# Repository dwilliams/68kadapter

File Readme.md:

# 68030 to 68020 adapter

Barebones adapter for Motorola processors, converting 68030 to 68020. There is no logic in this, and all the extra features of the 68030 are disabled.

# Why was this made?

To be used with [https://rosco-m68k.com/](https://rosco-m68k.com/) 68020 SBC to test CPUs bought off eBay. Didn't want to buy both the '20 and the '30 version, and now I can test (to a large degree) both versions. The MMU isn't getting tested, but in practice the chips either all work or fail completely to even come up, so it met it's goal.

# Headers and socket

You can buy those off sites like DigiKey or eBay.

For the plug-in 68020 side I used 2.54 mm Single Row Male Pin Headers that I cut up to fill in the rows/columns as needed. They need to be aligned really well otherwise it's close to impossible to plug them into a socket. I used one of the non-populated boards (got 3 made for corrections, test, etc) to hold the pins in place in the right way, but you can also use a 68020 socket and get the same effect. The latter might be too much of a heat sink though, making soldering hard.

The 68030 side is just a regular 128 Pin Machine Pin Grid Array PGA IC Socket.

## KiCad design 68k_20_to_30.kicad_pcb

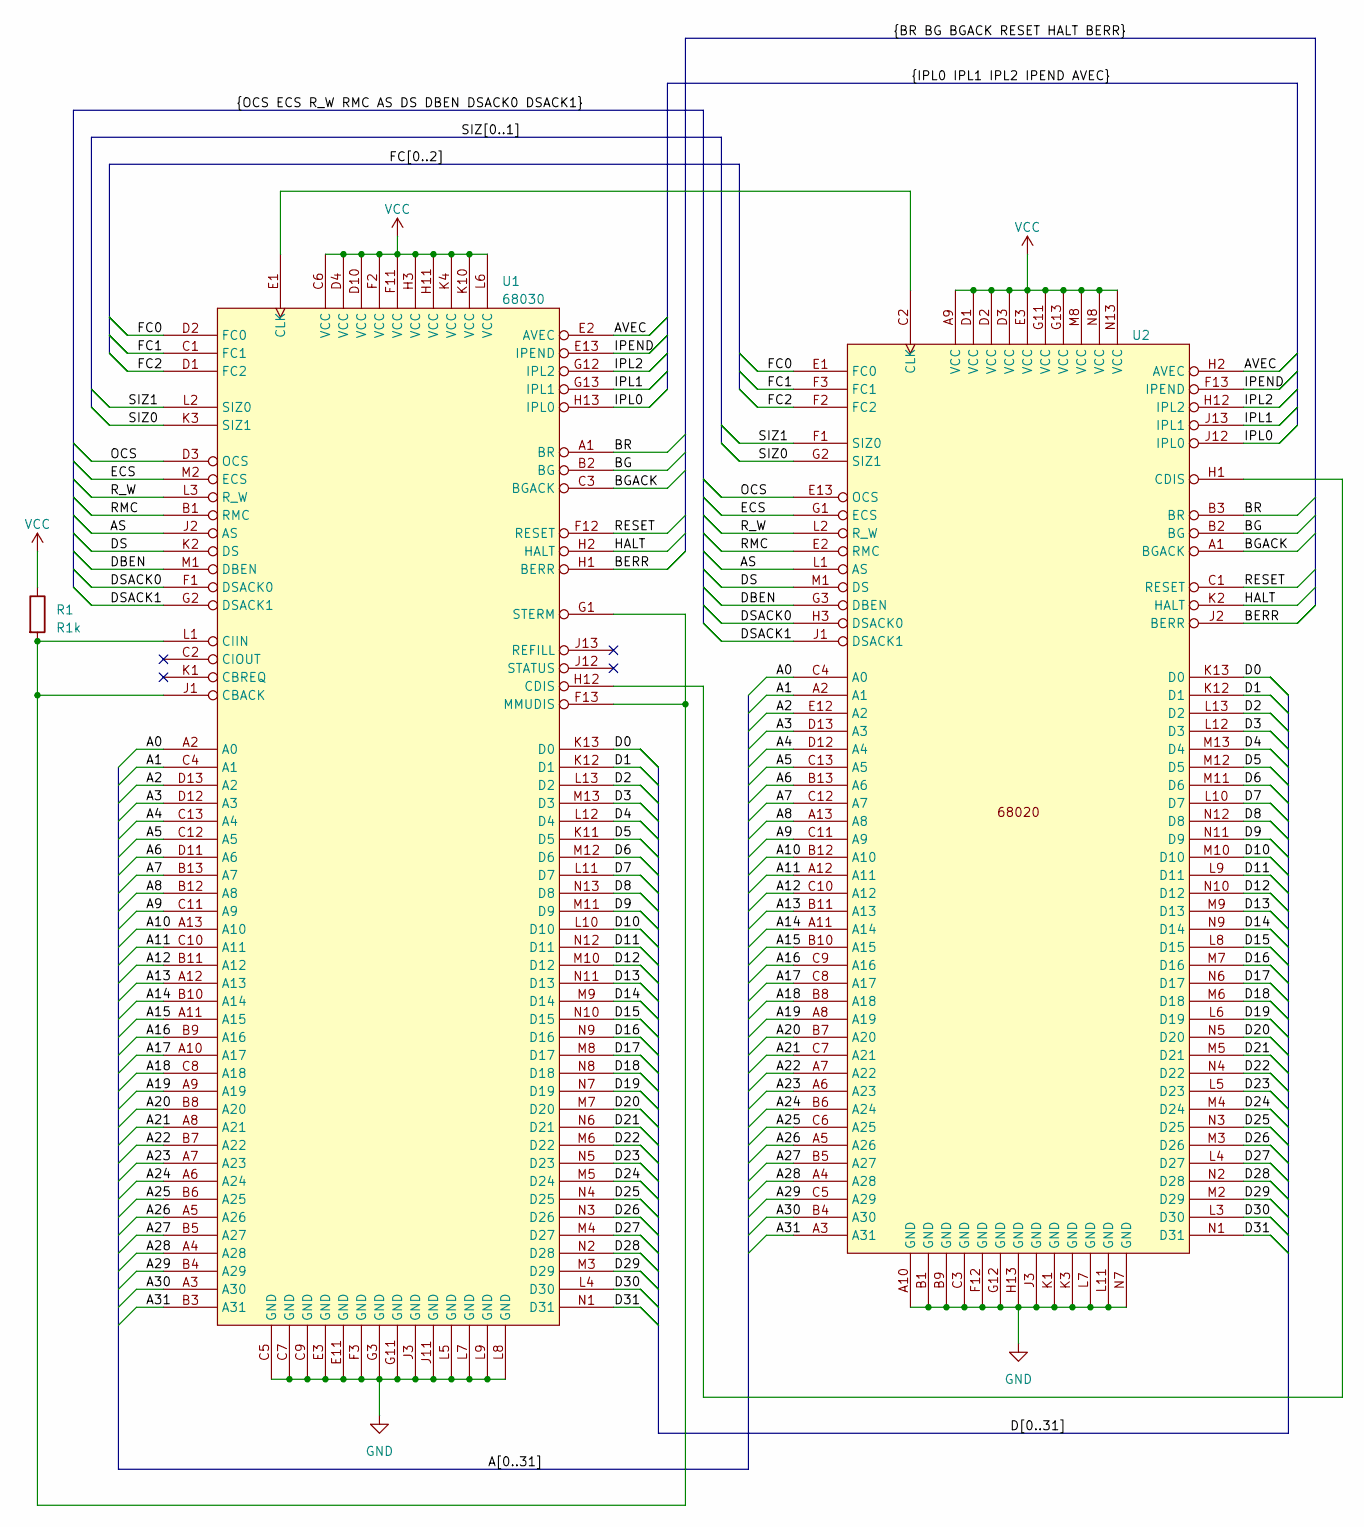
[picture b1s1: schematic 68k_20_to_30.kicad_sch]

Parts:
R1: R1k; R_Axial_DIN0204_L3.6mm_D1.6mm_P5.08mm_Horizontal
U1: 68030; PGA114_68030
U2: PGA114_68020

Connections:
/A0: U1.A2 (A0), U2.C4 (A0)
/A1: U1.C4 (A1), U2.A2 (A1)
/A2: U1.D13 (A2), U2.E12 (A2)
/A3: U1.D12 (A3), U2.D13 (A3)
/A4: U1.C13 (A4), U2.D12 (A4)
/A5: U1.C12 (A5), U2.C13 (A5)
/A6: U1.D11 (A6), U2.B13 (A6)
/A7: U1.B13 (A7), U2.C12 (A7)
/A8: U1.B12 (A8), U2.A13 (A8)
/A9: U1.C11 (A9), U2.C11 (A9)
/A10: U1.A13 (A10), U2.B12 (A10)
/A11: U1.C10 (A11), U2.A12 (A11)
/A12: U1.B11 (A12), U2.C10 (A12)
/A13: U1.A12 (A13), U2.B11 (A13)
/A14: U1.B10 (A14), U2.A11 (A14)
/A15: U1.A11 (A15), U2.B10 (A15)
/A16: U1.B9 (A16), U2.C9 (A16)
/A17: U1.A10 (A17), U2.C8 (A17)
/A18: U1.C8 (A18), U2.B8 (A18)
/A19: U1.A9 (A19), U2.A8 (A19)
/A20: U1.B8 (A20), U2.B7 (A20)
/A21: U1.A8 (A21), U2.C7 (A21)
/A22: U1.B7 (A22), U2.A7 (A22)
/A23: U1.A7 (A23), U2.A6 (A23)
/A24: U1.A6 (A24), U2.B6 (A24)
/A25: U1.B6 (A25), U2.C6 (A25)
/A26: U1.A5 (A26), U2.A5 (A26)
/A27: U1.B5 (A27), U2.B5 (A27)
/A28: U1.A4 (A28), U2.A4 (A28)
/A29: U1.B4 (A29), U2.C5 (A29)
/A30: U1.A3 (A30), U2.B4 (A30)
/A31: U1.B3 (A31), U2.A3 (A31)
/AS: U1.J2 (AS), U2.L1 (AS)
/AVEC: U1.E2 (AVEC), U2.H2 (AVEC)
/BERR: U1.H1 (BERR), U2.J2 (BERR)
/BG: U1.B2 (BG), U2.B2 (BG)
/BGACK: U1.C3 (BGACK), U2.A1 (BGACK)
/BR: U1.A1 (BR), U2.B3 (BR)
/D0: U1.K13 (D0), U2.K13 (D0)
/D1: U1.K12 (D1), U2.K12 (D1)
/D2: U1.L13 (D2), U2.L13 (D2)
/D3: U1.M13 (D3), U2.L12 (D3)
/D4: U1.L12 (D4), U2.M13 (D4)
/D5: U1.K11 (D5), U2.M12 (D5)
/D6: U1.M12 (D6), U2.M11 (D6)
/D7: U1.L11 (D7), U2.L10 (D7)
/D8: U1.N13 (D8), U2.N12 (D8)
/D9: U1.M11 (D9), U2.N11 (D9)
/D10: U1.L10 (D10), U2.M10 (D10)
/D11: U1.N12 (D11), U2.L9 (D11)
/D12: U1.M10 (D12), U2.N10 (D12)
/D13: U1.N11 (D13), U2.M9 (D13)
/D14: U1.M9 (D14), U2.N9 (D14)
/D15: U1.N10 (D15), U2.L8 (D15)
/D16: U1.N9 (D16), U2.M7 (D16)
/D17: U1.M8 (D17), U2.N6 (D17)
/D18: U1.N8 (D18), U2.M6 (D18)
/D19: U1.N7 (D19), U2.L6 (D19)
/D20: U1.M7 (D20), U2.N5 (D20)
/D21: U1.N6 (D21), U2.M5 (D21)
/D22: U1.M6 (D22), U2.N4 (D22)
/D23: U1.N5 (D23), U2.L5 (D23)
/D24: U1.M5 (D24), U2.M4 (D24)
/D25: U1.N4 (D25), U2.N3 (D25)
/D26: U1.N3 (D26), U2.M3 (D26)
/D27: U1.M4 (D27), U2.L4 (D27)
/D28: U1.N2 (D28), U2.N2 (D28)
/D29: U1.M3 (D29), U2.M2 (D29)
/D30: U1.L4 (D30), U2.L3 (D30)
/D31: U1.N1 (D31), U2.N1 (D31)
/DBEN: U1.M1 (DBEN), U2.G3 (DBEN)
/DS: U1.K2 (DS), U2.M1 (DS)
/DSACK0: U1.F1 (DSACK0), U2.H3 (DSACK0)
/DSACK1: U1.G2 (DSACK1), U2.J1 (DSACK1)
/ECS: U1.M2 (ECS), U2.G1 (ECS)
/FC0: U1.D2 (FC0), U2.E1 (FC0)
/FC1: U1.C1 (FC1), U2.F3 (FC1)
/FC2: U1.D1 (FC2), U2.F2 (FC2)
/HALT: U1.H2 (HALT), U2.K2 (HALT)
/IPEND: U1.E13 (IPEND), U2.F13 (IPEND)
/IPL0: U1.H13 (IPL0), U2.J12 (IPL0)
/IPL1: U1.G13 (IPL1), U2.J13 (IPL1)
/IPL2: U1.G12 (IPL2), U2.H12 (IPL2)
/OCS: U1.D3 (OCS), U2.E13 (OCS)
/RESET: U1.F12 (RESET), U2.C1 (RESET)
/RMC: U1.B1 (RMC), U2.E2 (RMC)
/R_W: U1.L3 (R_W), U2.L2 (R_W)
/SIZ0: U1.K3 (SIZ1), U2.G2 (SIZ1)
/SIZ1: U1.L2 (SIZ0), U2.F1 (SIZ0)
GND: U1.C5 (GND), U1.C7 (GND), U1.C9 (GND), U1.E3 (GND), U1.E11 (GND), U1.F3 (GND), U1.G3 (GND), U1.G11 (GND), U1.J3 (GND), U1.J11 (GND), U1.L5 (GND), U1.L7 (GND), U1.L8 (GND), U1.L9 (GND), U2.A10 (GND), U2.B1 (GND), U2.B9 (GND), U2.C3 (GND), U2.F12 (GND), U2.G12 (GND), U2.H13 (GND), U2.J3 (GND), U2.K1 (GND), U2.K3 (GND), U2.L7 (GND), U2.L11 (GND), U2.N7 (GND)
unnamed: R1.2, U1.F13 (MMUDIS), U1.G1 (STERM), U1.J1 (CBACK), U1.L1 (CIIN)
unnamed: U1.H12 (CDIS), U2.H1 (CDIS)
unnamed: U1.E1 (CLK), U2.C2 (CLK)
VCC: R1.1, U1.C6 (VCC), U1.D4 (VCC), U1.D10 (VCC), U1.F2 (VCC), U1.F11 (VCC), U1.H3 (VCC), U1.H11 (VCC), U1.K4 (VCC), U1.K10 (VCC), U1.L6 (VCC), U2.A9 (VCC), U2.D1 (VCC), U2.D2 (VCC), U2.D3 (VCC), U2.E3 (VCC), U2.G11 (VCC), U2.G13 (VCC), U2.M8 (VCC), U2.N8 (VCC), U2.N13 (VCC)

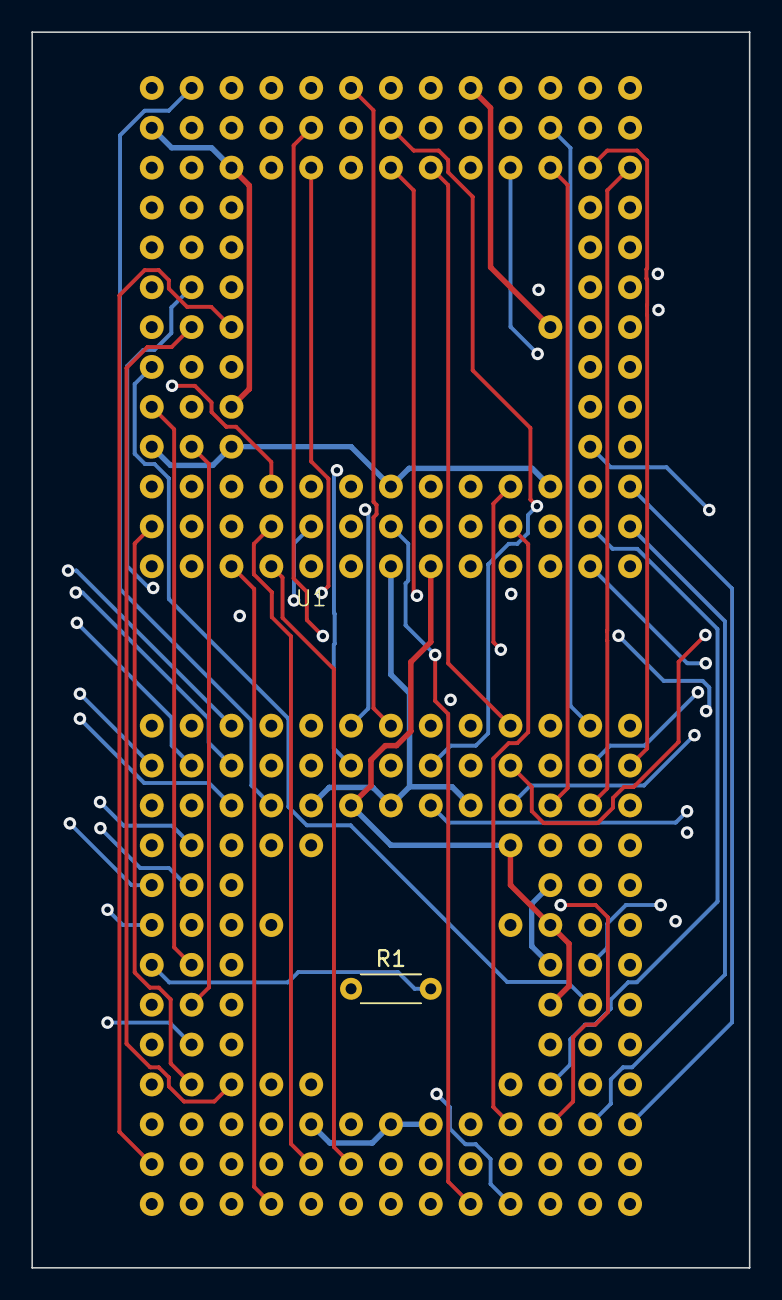
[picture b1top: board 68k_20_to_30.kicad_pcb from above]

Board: 4 copper layers, 45.7 x 78.7 mm, 3 parts (0 on the bottom side), 94 nets.

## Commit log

2025-02-13 Adding current state of routing.
